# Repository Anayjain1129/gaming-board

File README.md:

# Gaming board

### Why did I make it?
it like a split keeb but i just never completed it and it's still not completed all  that's left is firmware and it'll be done later.

Features:

- Raspberry Pi Pico
- Customised layout
- QMK firmware
- cool silkscreen
- Custom case

### Schematic

### PCB 

### Case

The firmware is still left and i'll do it ASAP

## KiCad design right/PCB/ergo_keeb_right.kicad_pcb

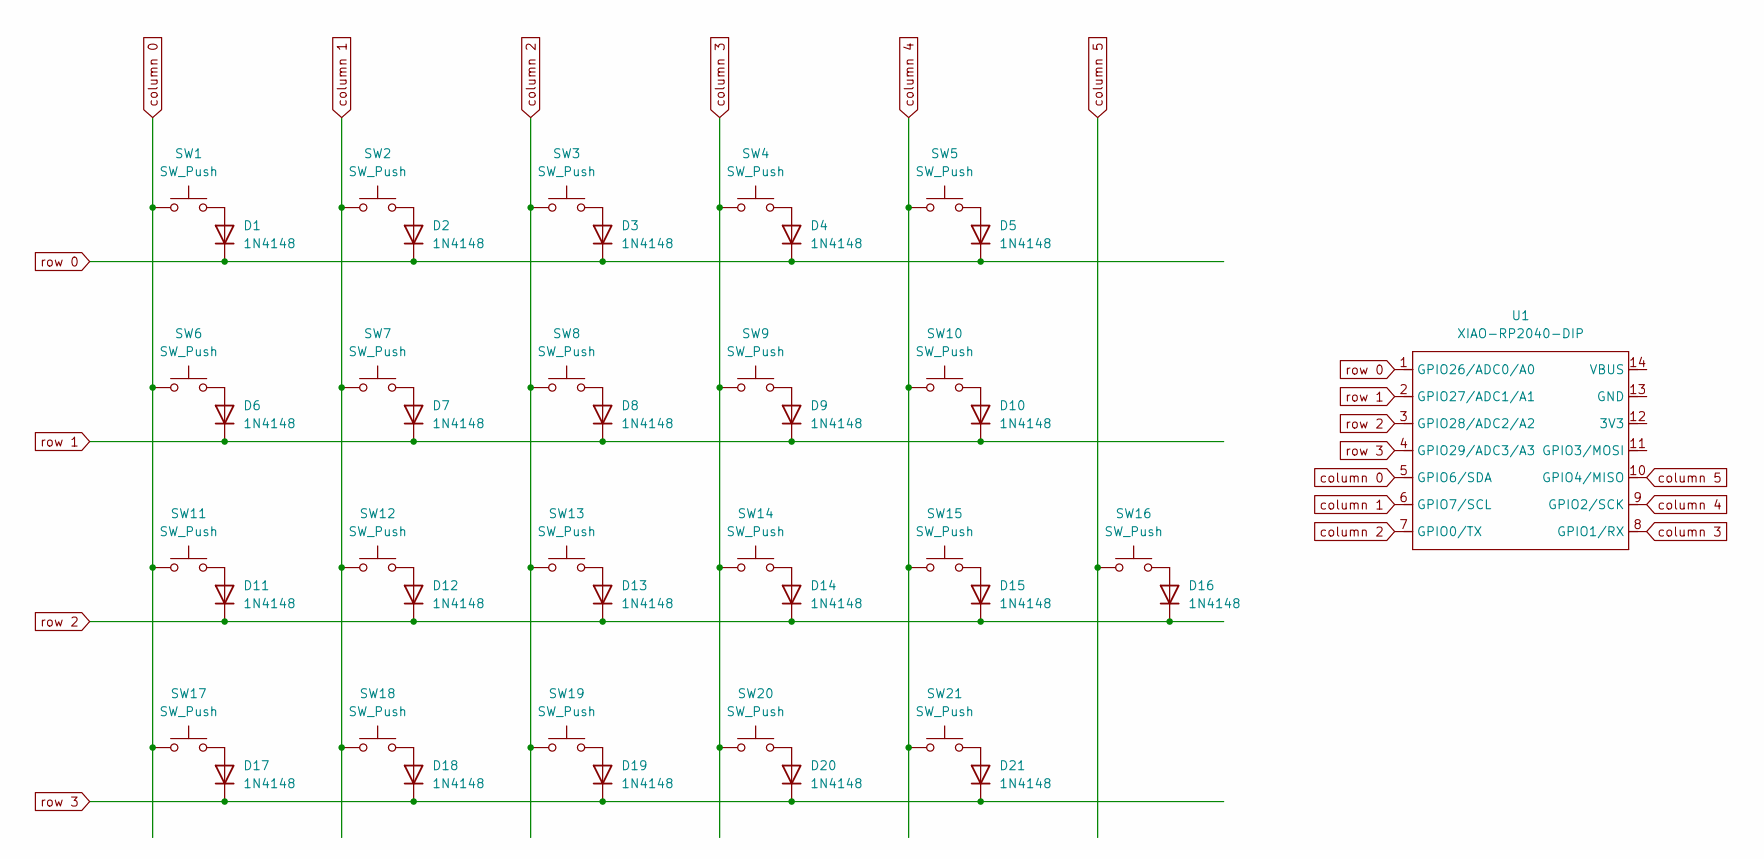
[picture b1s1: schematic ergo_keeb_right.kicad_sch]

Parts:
D1, D2, D3, D4, D5, D6, D7, D8, D9, D10, D11, D12, D13, D14, D15, D16, D17, D18, D19, D20, D21: 1N4148; D_DO-35_SOD27_P7.62mm_Horizontal
SW1, SW2, SW3, SW4, SW5, SW6, SW7, SW8, SW9, SW10, SW11, SW12, SW13, SW14, SW15, SW17, SW18, SW19, SW20, SW21: SW_Push; SW_Cherry_MX_1.00u_PCB
SW16: SW_Push; SW_Cherry_MX_1.50u_PCB
U1: XIAO-RP2040-DIP

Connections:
unnamed: D1.2 (A), SW1.2
unnamed: D2.2 (A), SW2.2
unnamed: D3.2 (A), SW3.2
unnamed: D4.2 (A), SW4.2
unnamed: D5.2 (A), SW5.2
unnamed: D6.2 (A), SW6.2
unnamed: D7.2 (A), SW7.2
unnamed: D8.2 (A), SW8.2
unnamed: D9.2 (A), SW9.2
unnamed: D10.2 (A), SW10.2
unnamed: D11.2 (A), SW11.2
unnamed: D12.2 (A), SW12.2
unnamed: D13.2 (A), SW13.2
unnamed: D14.2 (A), SW14.2
unnamed: D15.2 (A), SW15.2
unnamed: D16.2 (A), SW16.2
unnamed: D17.2 (A), SW17.2
unnamed: D18.2 (A), SW18.2
unnamed: D19.2 (A), SW19.2
unnamed: D20.2 (A), SW20.2
unnamed: D21.2 (A), SW21.2
column 0: SW1.1, SW6.1, SW11.1, SW17.1, U1.5 (GPIO6/SDA)
column 1: SW2.1, SW7.1, SW12.1, SW18.1, U1.6 (GPIO7/SCL)
column 2: SW3.1, SW8.1, SW13.1, SW19.1, U1.7 (GPIO0/TX)
column 3: SW4.1, SW9.1, SW14.1, SW20.1, U1.8 (GPIO1/RX)
column 4: SW5.1, SW10.1, SW15.1, SW21.1, U1.9 (GPIO2/SCK)
column 5: SW16.1, U1.10 (GPIO4/MISO)
row 0: D1.1 (K), D2.1 (K), D3.1 (K), D4.1 (K), D5.1 (K), U1.1 (GPIO26/ADC0/A0)
row 1: D6.1 (K), D7.1 (K), D8.1 (K), D9.1 (K), D10.1 (K), U1.2 (GPIO27/ADC1/A1)
row 2: D11.1 (K), D12.1 (K), D13.1 (K), D14.1 (K), D15.1 (K), D16.1 (K), U1.3 (GPIO28/ADC2/A2)
row 3: D17.1 (K), D18.1 (K), D19.1 (K), D20.1 (K), D21.1 (K), U1.4 (GPIO29/ADC3/A3)

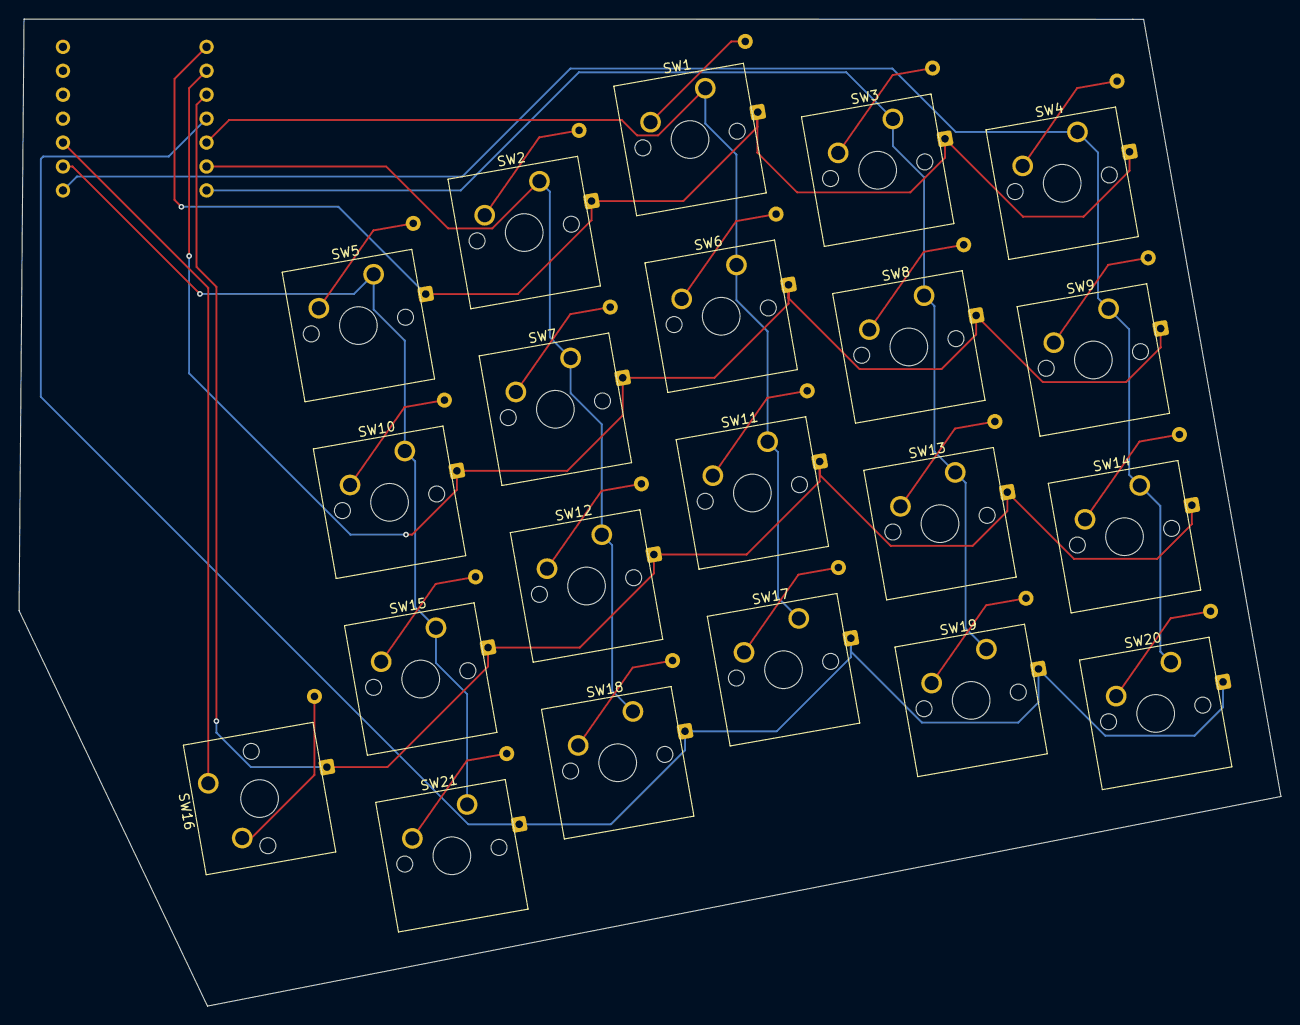
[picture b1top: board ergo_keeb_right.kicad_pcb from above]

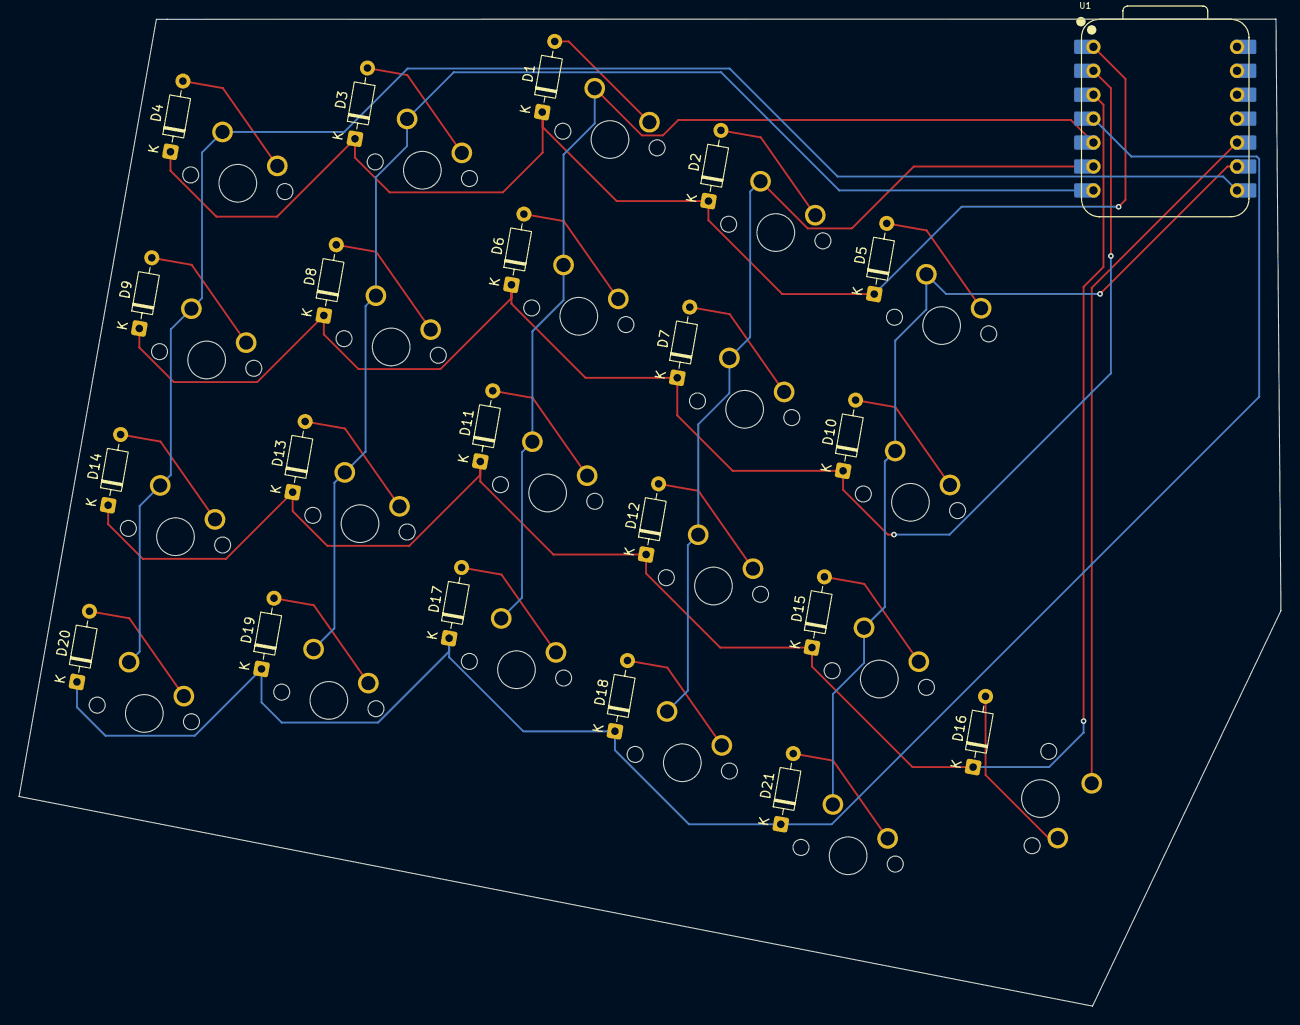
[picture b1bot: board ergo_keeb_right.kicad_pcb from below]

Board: 2 copper layers, 134.0 x 104.8 mm, 43 parts (22 on the bottom side), 31 nets.

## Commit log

2026-01-28 Fix image links in README for PCB section.
    Updated image links in the PCB section to use URL encoding.
